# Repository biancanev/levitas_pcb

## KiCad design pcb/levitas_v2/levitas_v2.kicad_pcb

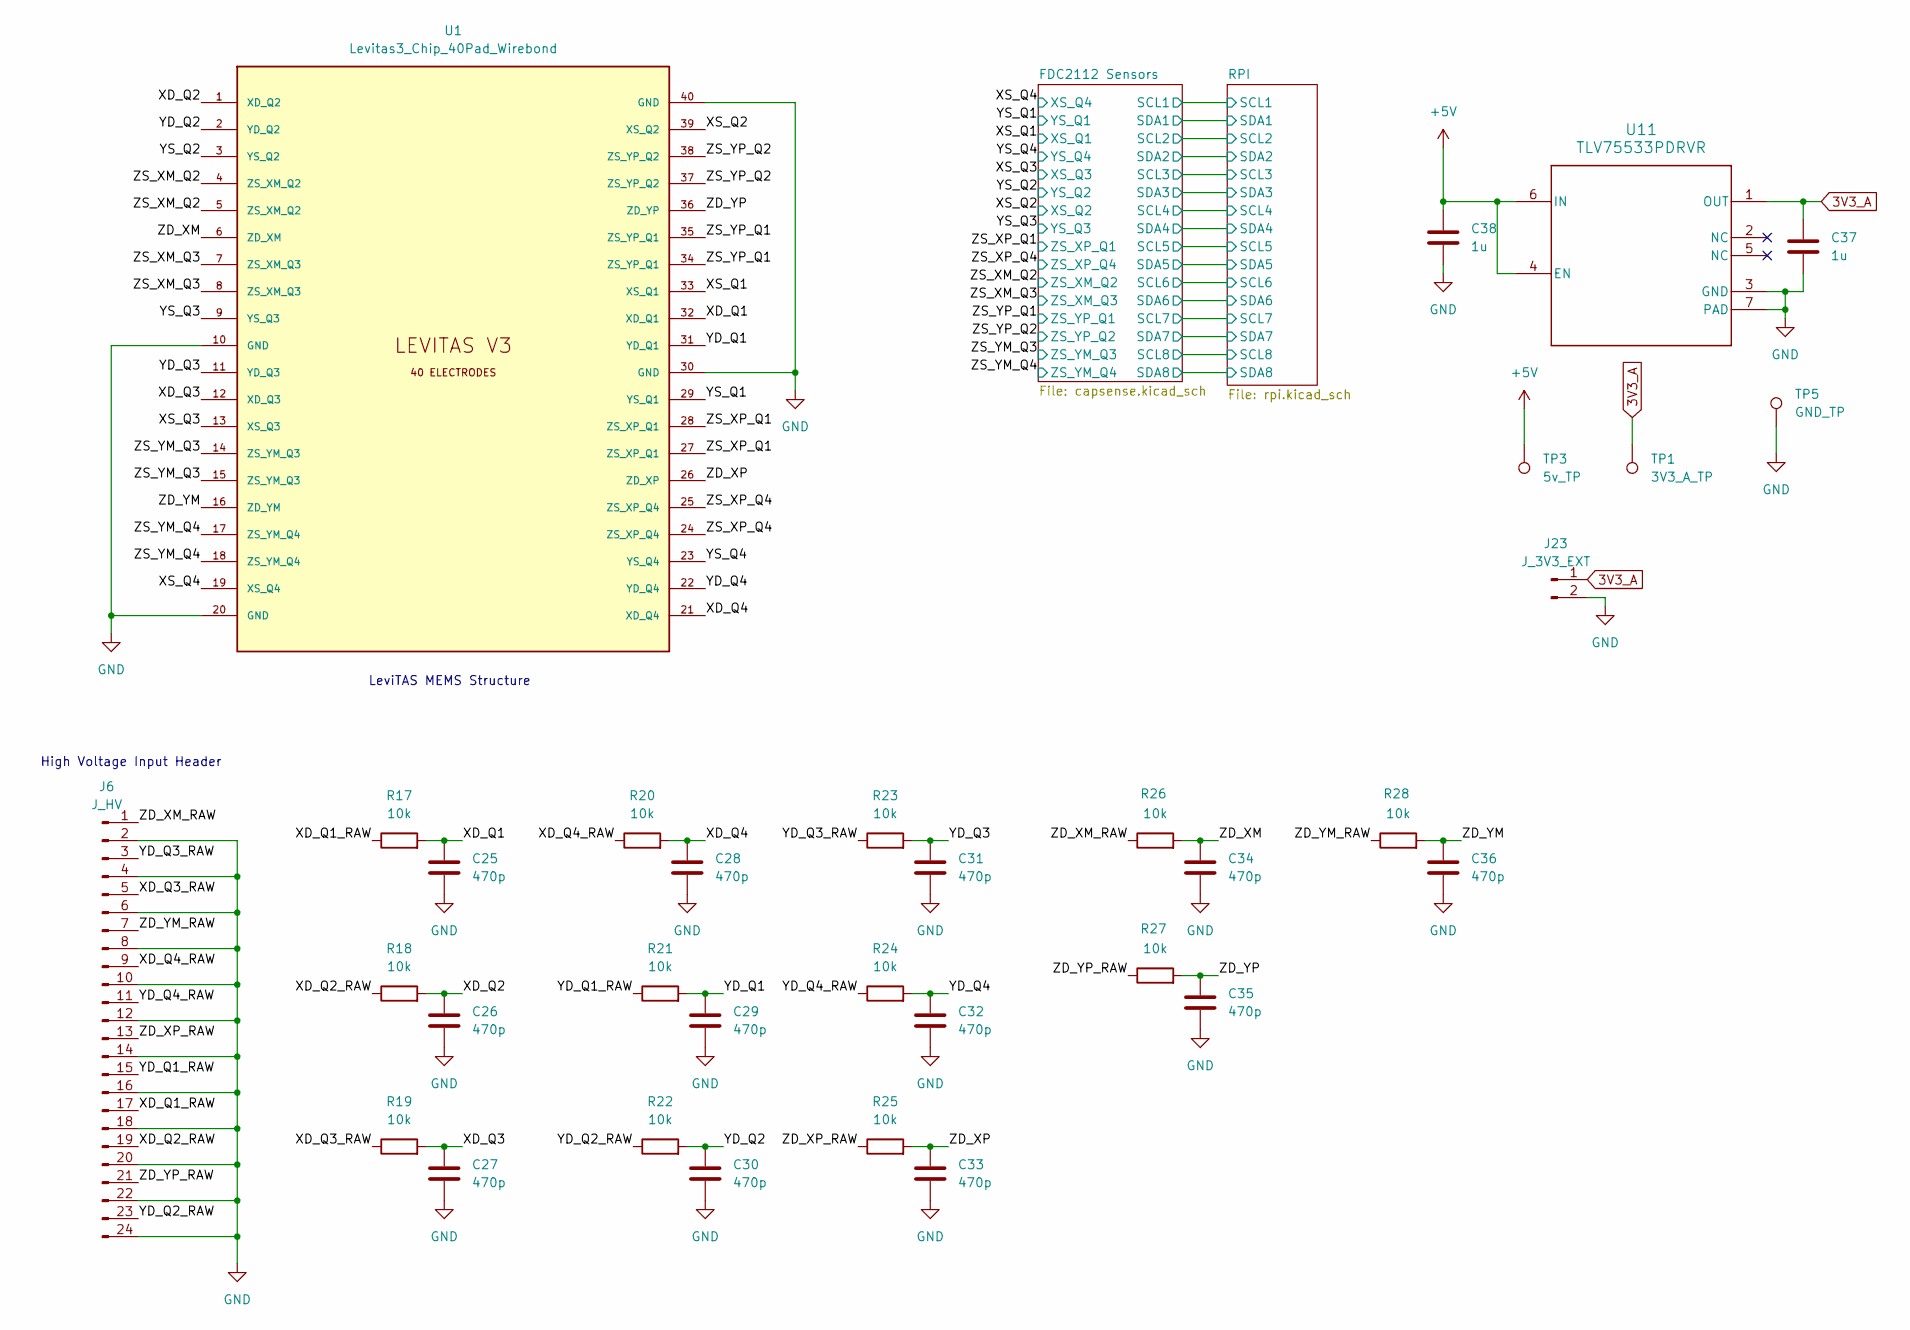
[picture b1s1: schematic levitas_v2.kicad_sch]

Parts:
C25, C26, C27, C28, C29, C30, C31, C32, C33, C34, C35, C36: 470p; C_0805_2012Metric
C37, C38: 1u; C_0805_2012Metric
J6: J_HV; PinHeader_1x24_P2.54mm_Vertical
J23: J_3V3_EXT; PinHeader_1x02_P2.54mm_Vertical
R17, R18, R19, R20, R21, R22, R23, R24, R25, R26, R27, R28: 10k; R_1206_3216Metric
TP1: 3V3_A_TP; TestPoint_Pad_D1.0mm
TP3: 5v_TP; TestPoint_Pad_D1.0mm
TP5: GND_TP; TestPoint_Pad_D1.0mm
U1: Levitas3_Chip_40Pad_Wirebond
U11: TLV75533PDRVR; DRV0006A

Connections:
/XD_Q1: C25.1, R17.2, U1.32 (XD_Q1)
/XD_Q1_RAW: J6.17, R17.1
/XD_Q2: C26.1, R18.2, U1.1 (XD_Q2)
/XD_Q2_RAW: J6.19, R18.1
/XD_Q3: C27.1, R19.2, U1.12 (XD_Q3)
/XD_Q3_RAW: J6.5, R19.1
/XD_Q4: C28.1, R20.2, U1.21 (XD_Q4)
/XD_Q4_RAW: J6.9, R20.1
/XS_Q1: U1.33 (XS_Q1); also elsewhere on the board
/XS_Q2: U1.39 (XS_Q2); also elsewhere on the board
/XS_Q3: U1.13 (XS_Q3); also elsewhere on the board
/XS_Q4: U1.19 (XS_Q4); also elsewhere on the board
/YD_Q1: C29.1, R21.2, U1.31 (YD_Q1)
/YD_Q1_RAW: J6.15, R21.1
/YD_Q2: C30.1, R22.2, U1.2 (YD_Q2)
/YD_Q2_RAW: J6.23, R22.1
/YD_Q3: C31.1, R23.2, U1.11 (YD_Q3)
/YD_Q3_RAW: J6.3, R23.1
/YD_Q4: C32.1, R24.2, U1.22 (YD_Q4)
/YD_Q4_RAW: J6.11, R24.1
/YS_Q1: U1.29 (YS_Q1); also elsewhere on the board
/YS_Q2: U1.3 (YS_Q2); also elsewhere on the board
/YS_Q3: U1.9 (YS_Q3); also elsewhere on the board
/YS_Q4: U1.23 (YS_Q4); also elsewhere on the board
/ZD_XM: C34.1, R26.2, U1.6 (ZD_XM)
/ZD_XM_RAW: J6.1, R26.1
/ZD_XP: C33.1, R25.2, U1.26 (ZD_XP)
/ZD_XP_RAW: J6.13, R25.1
/ZD_YM: C36.1, R28.2, U1.16 (ZD_YM)
/ZD_YM_RAW: J6.7, R28.1
/ZD_YP: C35.1, R27.2, U1.36 (ZD_YP)
/ZD_YP_RAW: J6.21, R27.1
/ZS_XM_Q2: U1.4 (ZS_XM_Q2), U1.5 (ZS_XM_Q2); also elsewhere on the board
/ZS_XM_Q3: U1.7 (ZS_XM_Q3), U1.8 (ZS_XM_Q3); also elsewhere on the board
/ZS_XP_Q1: U1.27 (ZS_XP_Q1), U1.28 (ZS_XP_Q1); also elsewhere on the board
/ZS_XP_Q4: U1.24 (ZS_XP_Q4), U1.25 (ZS_XP_Q4); also elsewhere on the board
/ZS_YM_Q3: U1.14 (ZS_YM_Q3), U1.15 (ZS_YM_Q3); also elsewhere on the board
/ZS_YM_Q4: U1.17 (ZS_YM_Q4), U1.18 (ZS_YM_Q4); also elsewhere on the board
/ZS_YP_Q1: U1.34 (ZS_YP_Q1), U1.35 (ZS_YP_Q1); also elsewhere on the board
/ZS_YP_Q2: U1.37 (ZS_YP_Q2), U1.38 (ZS_YP_Q2); also elsewhere on the board
GND: C25.2, C26.2, C27.2, C28.2, C29.2, C30.2, C31.2, C32.2, C33.2, C34.2, C35.2, C36.2, C37.2, C38.2, J6.2, J6.4, J6.6, J6.8, J6.10, J6.12, J6.14, J6.16, J6.18, J6.20, J6.22, J6.24, J23.2, TP5.1 (1_1), U1.10 (GND), U1.20 (GND), U1.30 (GND), U1.40 (GND), U11.3 (GND), U11.7 (PAD); also elsewhere on the board

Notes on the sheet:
High Voltage Input Header
LeviTAS MEMS Structure

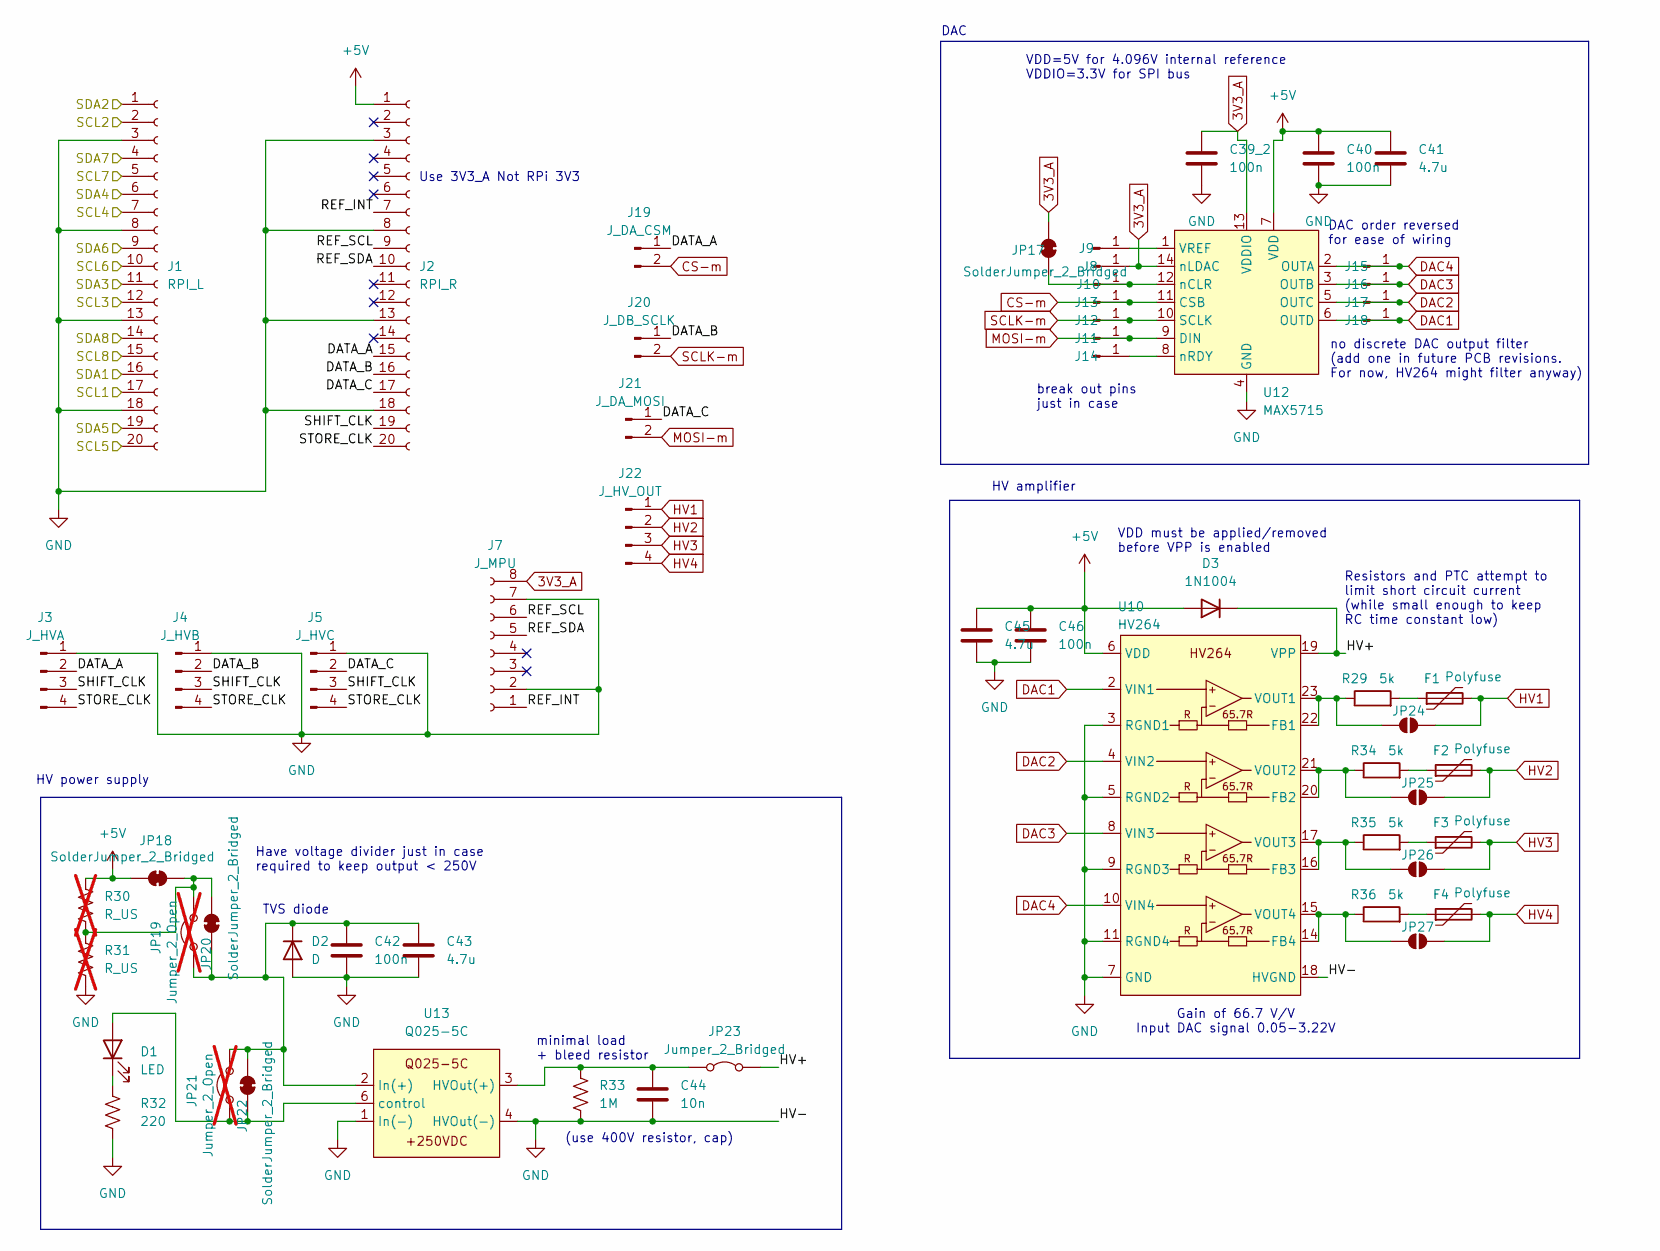
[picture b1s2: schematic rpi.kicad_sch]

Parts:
C39_2, C40, C42, C46: 100n; C_0603_1608Metric
C41, C43, C45: 4.7u; C_0805_2012Metric
C44: 10n; C_Disc_D7.5mm_W2.5mm_P5.00mm
D1: LED; LED_D5.0mm
D2: D; D_DO-41_SOD81_P10.16mm_Horizontal
D3: 1N1004; D_DO-41_SOD81_P10.16mm_Horizontal
F1, F2, F3, F4: Polyfuse; R_Axial_DIN0207_L6.3mm_D2.5mm_P7.62mm_Horizontal
J1: RPI_L; PinSocket_1x20_P2.54mm_Vertical
J2: RPI_R; PinSocket_1x20_P2.54mm_Vertical
J3: J_HVA; PinHeader_1x04_P2.54mm_Vertical
J4: J_HVB; PinHeader_1x04_P2.54mm_Vertical
J5: J_HVC; PinHeader_1x04_P2.54mm_Vertical
J7: J_MPU; PinSocket_1x08_P2.54mm_Vertical
J8, J9, J10, J11, J12, J13, J14, J15, J16, J17, J18: Conn_01x01_Pin; TestPoint_Pad_D2.0mm
J19: J_DA_CSM; PinHeader_1x02_P2.54mm_Vertical
J20: J_DB_SCLK; PinHeader_1x02_P2.54mm_Vertical
J21: J_DA_MOSI; PinHeader_1x02_P2.54mm_Vertical
J22: J_HV_OUT; PinHeader_1x04_P2.54mm_Vertical
JP17, JP18, JP20, JP22: SolderJumper_2_Bridged; SolderJumper-2_P1.3mm_Bridged_RoundedPad1.0x1.5mm
JP19, JP21: Jumper_2_Open; PinHeader_1x02_P2.54mm_Vertical; not fitted
JP23: Jumper_2_Bridged; PinHeader_1x02_P2.54mm_Vertical
JP24, JP25, JP26, JP27: SolderJumper_2_Open; SolderJumper-2_P1.3mm_Open_RoundedPad1.0x1.5mm
R29, R34, R35, R36: 5k; R_Axial_DIN0207_L6.3mm_D2.5mm_P7.62mm_Horizontal
R30, R31: R_US; R_Axial_DIN0207_L6.3mm_D2.5mm_P7.62mm_Horizontal; not fitted
R32: 220; R_Axial_DIN0207_L6.3mm_D2.5mm_P7.62mm_Horizontal
R33: 1M; R_Axial_DIN0207_L6.3mm_D2.5mm_P7.62mm_Horizontal
U10: HV264; TSSOP-24_4.4x7.8mm_P0.65mm
U12: MAX5715; TSSOP-14_4.4x5mm_P0.65mm
U13: Q025-5C

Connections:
/FDC2112 Sensors/SCL1: J1.17; also elsewhere on the board
/FDC2112 Sensors/SCL2: J1.2; also elsewhere on the board
/FDC2112 Sensors/SCL3: J1.12; also elsewhere on the board
/FDC2112 Sensors/SCL4: J1.7; also elsewhere on the board
/FDC2112 Sensors/SCL5: J1.20; also elsewhere on the board
/FDC2112 Sensors/SCL6: J1.10; also elsewhere on the board
/FDC2112 Sensors/SCL7: J1.5; also elsewhere on the board
/FDC2112 Sensors/SCL8: J1.15; also elsewhere on the board
/FDC2112 Sensors/SDA1: J1.16; also elsewhere on the board
/FDC2112 Sensors/SDA2: J1.1; also elsewhere on the board
/FDC2112 Sensors/SDA3: J1.11; also elsewhere on the board
/FDC2112 Sensors/SDA4: J1.6; also elsewhere on the board
/FDC2112 Sensors/SDA5: J1.19; also elsewhere on the board
/FDC2112 Sensors/SDA6: J1.9; also elsewhere on the board
/FDC2112 Sensors/SDA7: J1.4; also elsewhere on the board
/FDC2112 Sensors/SDA8: J1.14; also elsewhere on the board
/RPI/DATA_A: J2.15, J3.2, J19.1
/RPI/DATA_B: J2.16, J4.2, J20.1
/RPI/DATA_C: J2.17, J5.2, J21.1
/RPI/HV+: D3.1 (K), JP23.2 (B), U10.19 (VPP)
/RPI/REF_INT: J2.7, J7.1
/RPI/REF_SCL: J2.9, J7.6
/RPI/REF_SDA: J2.10, J7.5
/RPI/SHIFT_CLK: J2.19, J3.3, J4.3, J5.3
/RPI/STORE_CLK: J2.20, J3.4, J4.4, J5.4
CS-m: J13.1, J19.2, U12.11 (CSB)
DAC1: J18.1, U10.2 (VIN1), U12.6 (OUTD)
DAC2: J17.1, U10.4 (VIN2), U12.5 (OUTC)
DAC3: J16.1, U10.8 (VIN3), U12.3 (OUTB)
DAC4: J15.1, U10.10 (VIN4), U12.2 (OUTA)
GND: C39_2.2, C40.2, C41.2, C42.2, C43.2, C44.2, C45.2, C46.2, D2.2 (A), J1.3, J1.8, J1.13, J1.18, J2.3, J2.8, J2.13, J2.18, J3.1, J4.1, J5.1, J7.2, J7.7, R31.2, R32.2, R33.2, U10.3 (RGND1), U10.5 (RGND2), U10.7 (GND), U10.9 (RGND3), U10.11 (RGND4), U10.18 (HVGND), U12.4 (GND), U13.1 (In(-)), U13.4 (HVOut(-)); also elsewhere on the board
HV1: F1.2, J22.1, JP24.2 (B)
HV2: F2.2, J22.2, JP25.2 (B)
HV3: F3.2, J22.3, JP26.2 (B)
HV4: F4.2, J22.4, JP27.2 (B)
MOSI-m: J11.1, J21.2, U12.9 (DIN)
unnamed: D1.2 (A), JP21.1 (A), JP22.1 (A), U13.6 (control)
unnamed: D1.1 (K), R32.1
unnamed: C42.1, C43.1, D2.1 (K), JP19.1 (A), JP20.1 (A), JP21.2 (B), JP22.2 (B), U13.2 (In(+))
unnamed: F1.1, R29.2
unnamed: F2.1, R34.2
unnamed: F3.1, R35.2
unnamed: F4.1, R36.2
unnamed: J9.1, U12.1 (VREF)
unnamed: J10.1, JP17.2 (B), U12.12 (nCLR)
unnamed: J14.1, U12.8 (nRDY)
unnamed: JP18.1 (A), JP19.2 (B), JP20.2 (B), R30.2, R31.1
unnamed: C44.1, JP23.1 (A), R33.1, U13.3 (HVOut(+))
unnamed: JP24.1 (A), R29.1, U10.22 (FB1), U10.23 (VOUT1)
unnamed: JP25.1 (A), R34.1, U10.20 (FB2), U10.21 (VOUT2)
unnamed: JP26.1 (A), R35.1, U10.16 (FB3), U10.17 (VOUT3)
unnamed: JP27.1 (A), R36.1, U10.14 (FB4), U10.15 (VOUT4)
SCLK-m: J12.1, J20.2, U12.10 (SCLK)

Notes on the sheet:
VDD=5V for 4.096V internal reference VDDIO=3.3V for SPI bus
DAC
VDD must be applied/removed before VPP is enabled
Resistors and PTC attempt to limit short circuit current (while small enough to keep RC time constant low)
TVS diode
DAC order reversed for ease of wiring
minimal load + bleed resistor
Have voltage divider just in case required to keep output < 250V
HV power supply
(use 400V resistor, cap)
break out pins just in case
Use 3V3_A Not RPi 3V3
no discrete DAC output filter (add one in future PCB revisions. For now, HV264 might filter anyway)
Gain of 66.7 V/V Input DAC signal 0.05-3.22V
HV amplifier

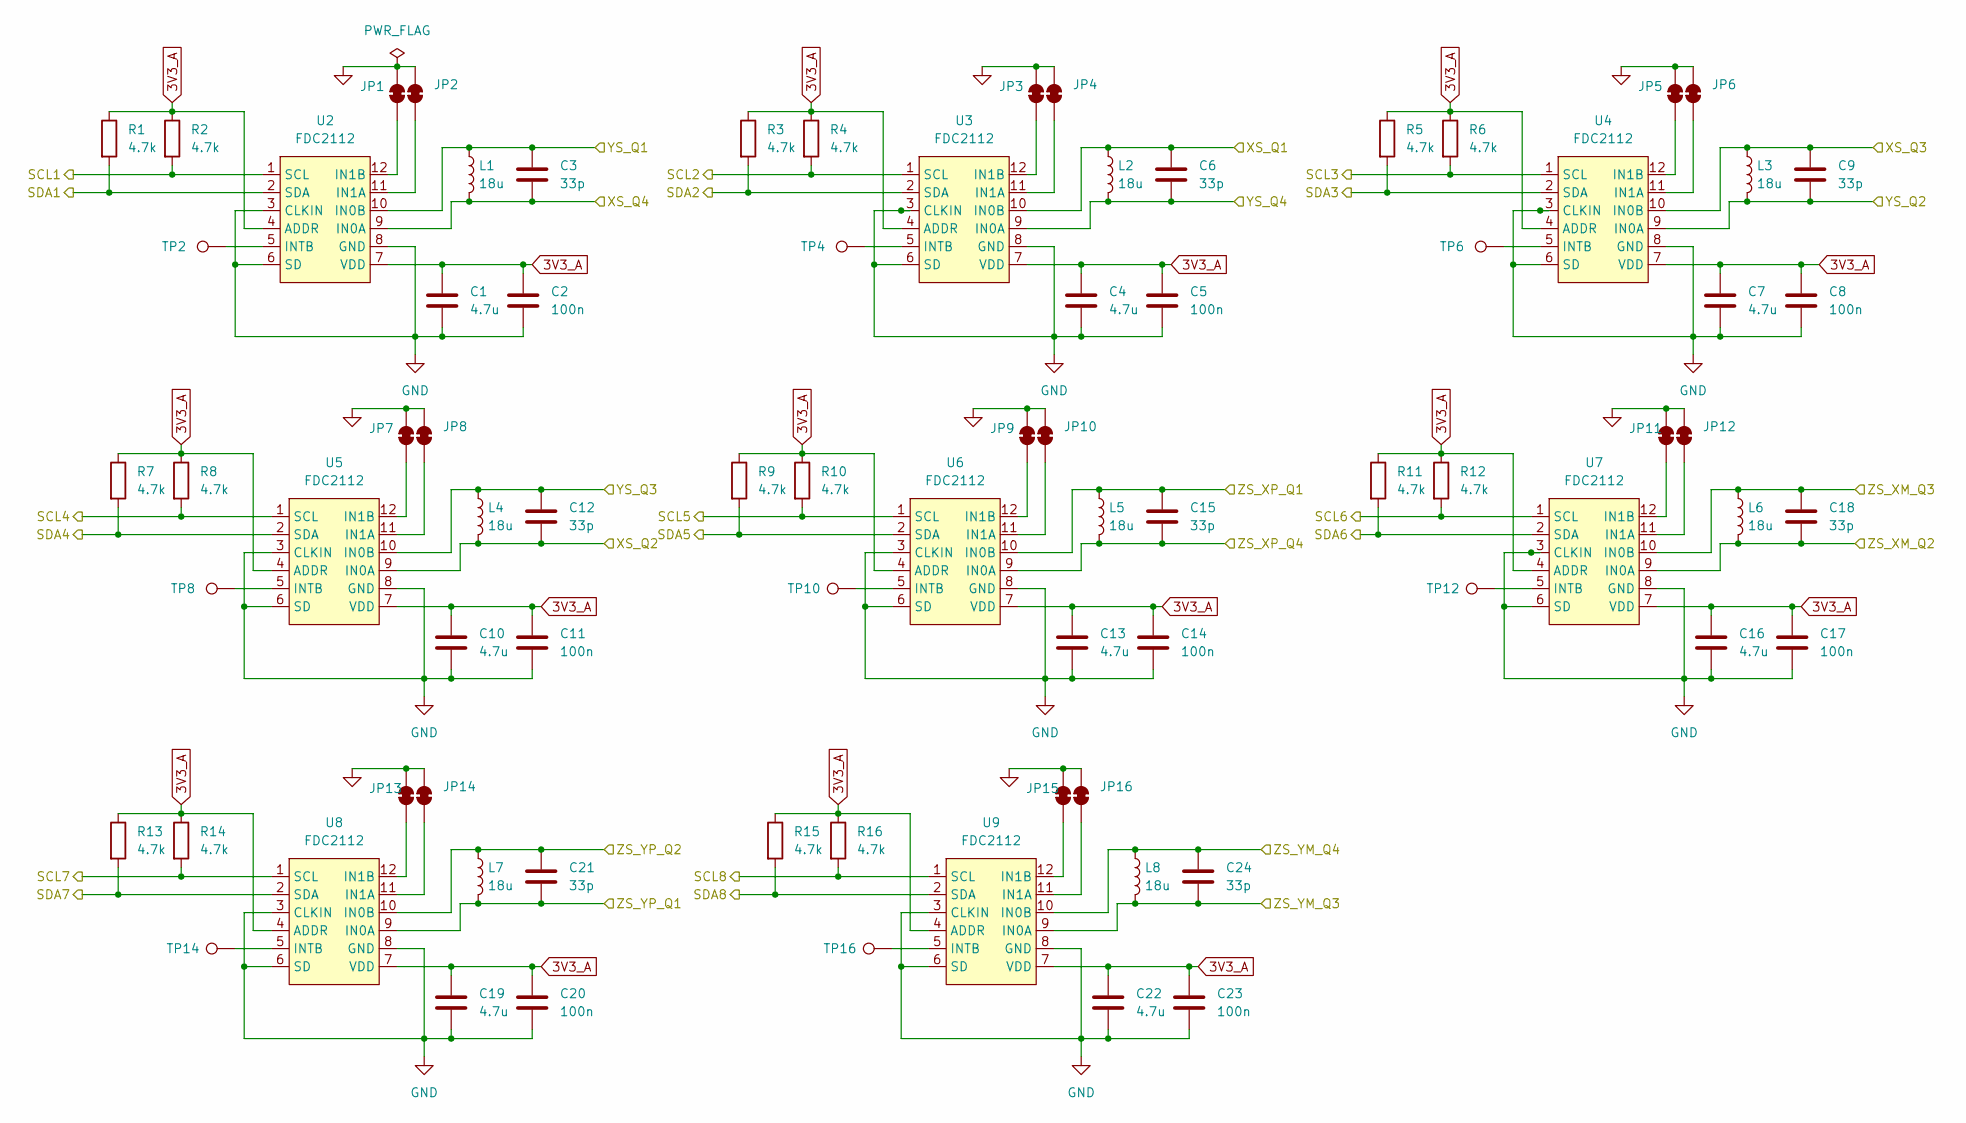
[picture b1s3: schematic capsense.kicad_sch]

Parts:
C1, C4, C7, C10, C13, C16, C19, C22: 4.7u; C_0805_2012Metric
C2, C5, C8, C11, C14, C17, C20, C23: 100n; C_0603_1608Metric
C3, C6, C9, C12, C15, C18, C21, C24: 33p; C_0603_1608Metric
JP1, JP2, JP3, JP4, JP5, JP6, JP7, JP8, JP9, JP10, JP11, JP12, JP13, JP14, JP15, JP16: SolderJumper_2_Bridged; SolderJumper-2_P1.3mm_Bridged_RoundedPad1.0x1.5mm
L1, L2, L3, L4, L5, L6, L7, L8: 18u; L_0603_1608Metric
R1, R2, R3, R4, R5, R6, R7, R8, R9, R10, R11, R12, R13, R14, R15, R16: 4.7k; R_0603_1608Metric
TP2, TP4, TP6, TP8, TP10, TP12, TP14, TP16: TestPoint; TestPoint_Pad_D1.0mm
U2, U3, U4, U5, U6, U7, U8, U9: FDC2112; WSON-12-1EP_4x4mm_P0.5mm_EP2.6x3mm

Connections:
/FDC2112 Sensors/SCL1: R2.2, U2.1 (SCL); also elsewhere on the board
/FDC2112 Sensors/SCL2: R4.2, U3.1 (SCL); also elsewhere on the board
/FDC2112 Sensors/SCL3: R6.2, U4.1 (SCL); also elsewhere on the board
/FDC2112 Sensors/SCL4: R8.2, U5.1 (SCL); also elsewhere on the board
/FDC2112 Sensors/SCL5: R10.2, U6.1 (SCL); also elsewhere on the board
/FDC2112 Sensors/SCL6: R12.2, U7.1 (SCL); also elsewhere on the board
/FDC2112 Sensors/SCL7: R14.2, U8.1 (SCL); also elsewhere on the board
/FDC2112 Sensors/SCL8: R16.2, U9.1 (SCL); also elsewhere on the board
/FDC2112 Sensors/SDA1: R1.2, U2.2 (SDA); also elsewhere on the board
/FDC2112 Sensors/SDA2: R3.2, U3.2 (SDA); also elsewhere on the board
/FDC2112 Sensors/SDA3: R5.2, U4.2 (SDA); also elsewhere on the board
/FDC2112 Sensors/SDA4: R7.2, U5.2 (SDA); also elsewhere on the board
/FDC2112 Sensors/SDA5: R9.2, U6.2 (SDA); also elsewhere on the board
/FDC2112 Sensors/SDA6: R11.2, U7.2 (SDA); also elsewhere on the board
/FDC2112 Sensors/SDA7: R13.2, U8.2 (SDA); also elsewhere on the board
/FDC2112 Sensors/SDA8: R15.2, U9.2 (SDA); also elsewhere on the board
/XS_Q1: C6.1, L2.1, U3.10 (IN0B); also elsewhere on the board
/XS_Q2: C12.2, L4.2, U5.9 (IN0A); also elsewhere on the board
/XS_Q3: C9.1, L3.1, U4.10 (IN0B); also elsewhere on the board
/XS_Q4: C3.2, L1.2, U2.9 (IN0A); also elsewhere on the board
/YS_Q1: C3.1, L1.1, U2.10 (IN0B); also elsewhere on the board
/YS_Q2: C9.2, L3.2, U4.9 (IN0A); also elsewhere on the board
/YS_Q3: C12.1, L4.1, U5.10 (IN0B); also elsewhere on the board
/YS_Q4: C6.2, L2.2, U3.9 (IN0A); also elsewhere on the board
/ZS_XM_Q2: C18.2, L6.2, U7.9 (IN0A); also elsewhere on the board
/ZS_XM_Q3: C18.1, L6.1, U7.10 (IN0B); also elsewhere on the board
/ZS_XP_Q1: C15.1, L5.1, U6.10 (IN0B); also elsewhere on the board
/ZS_XP_Q4: C15.2, L5.2, U6.9 (IN0A); also elsewhere on the board
/ZS_YM_Q3: C24.2, L8.2, U9.9 (IN0A); also elsewhere on the board
/ZS_YM_Q4: C24.1, L8.1, U9.10 (IN0B); also elsewhere on the board
/ZS_YP_Q1: C21.2, L7.2, U8.9 (IN0A); also elsewhere on the board
/ZS_YP_Q2: C21.1, L7.1, U8.10 (IN0B); also elsewhere on the board
GND: C1.2, C2.2, C4.2, C5.2, C7.2, C8.2, C10.2, C11.2, C13.2, C14.2, C16.2, C17.2, C19.2, C20.2, C22.2, C23.2, JP1.2 (B), JP2.2 (B), JP3.2 (B), JP4.2 (B), JP5.2 (B), JP6.2 (B), JP7.2 (B), JP8.2 (B), JP9.2 (B), JP10.2 (B), JP11.2 (B), JP12.2 (B), JP13.2 (B), JP14.2 (B), JP15.2 (B), JP16.2 (B), U2.3 (CLKIN), U2.6 (SD), U2.8 (GND), U3.3 (CLKIN), U3.6 (SD), U3.8 (GND), U4.3 (CLKIN), U4.6 (SD), U4.8 (GND), U5.3 (CLKIN), U5.6 (SD), U5.8 (GND), U6.3 (CLKIN), U6.6 (SD), U6.8 (GND), U7.3 (CLKIN), U7.6 (SD), U7.8 (GND), U8.3 (CLKIN), U8.6 (SD), U8.8 (GND), U9.3 (CLKIN), U9.6 (SD), U9.8 (GND); also elsewhere on the board
unnamed: JP1.1 (A), U2.12 (IN1B)
unnamed: JP2.1 (A), U2.11 (IN1A)
unnamed: JP3.1 (A), U3.12 (IN1B)
unnamed: JP4.1 (A), U3.11 (IN1A)
unnamed: JP5.1 (A), U4.12 (IN1B)
unnamed: JP6.1 (A), U4.11 (IN1A)
unnamed: JP7.1 (A), U5.12 (IN1B)
unnamed: JP8.1 (A), U5.11 (IN1A)
unnamed: JP9.1 (A), U6.12 (IN1B)
unnamed: JP10.1 (A), U6.11 (IN1A)
unnamed: JP11.1 (A), U7.12 (IN1B)
unnamed: JP12.1 (A), U7.11 (IN1A)
unnamed: JP13.1 (A), U8.12 (IN1B)
unnamed: JP14.1 (A), U8.11 (IN1A)
unnamed: JP15.1 (A), U9.12 (IN1B)
unnamed: JP16.1 (A), U9.11 (IN1A)
unnamed: TP2.1 (1_1), U2.5 (INTB)
unnamed: TP4.1 (1_1), U3.5 (INTB)
unnamed: TP6.1 (1_1), U4.5 (INTB)
unnamed: TP8.1 (1_1), U5.5 (INTB)
unnamed: TP10.1 (1_1), U6.5 (INTB)
unnamed: TP12.1 (1_1), U7.5 (INTB)
unnamed: TP14.1 (1_1), U8.5 (INTB)
unnamed: TP16.1 (1_1), U9.5 (INTB)

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
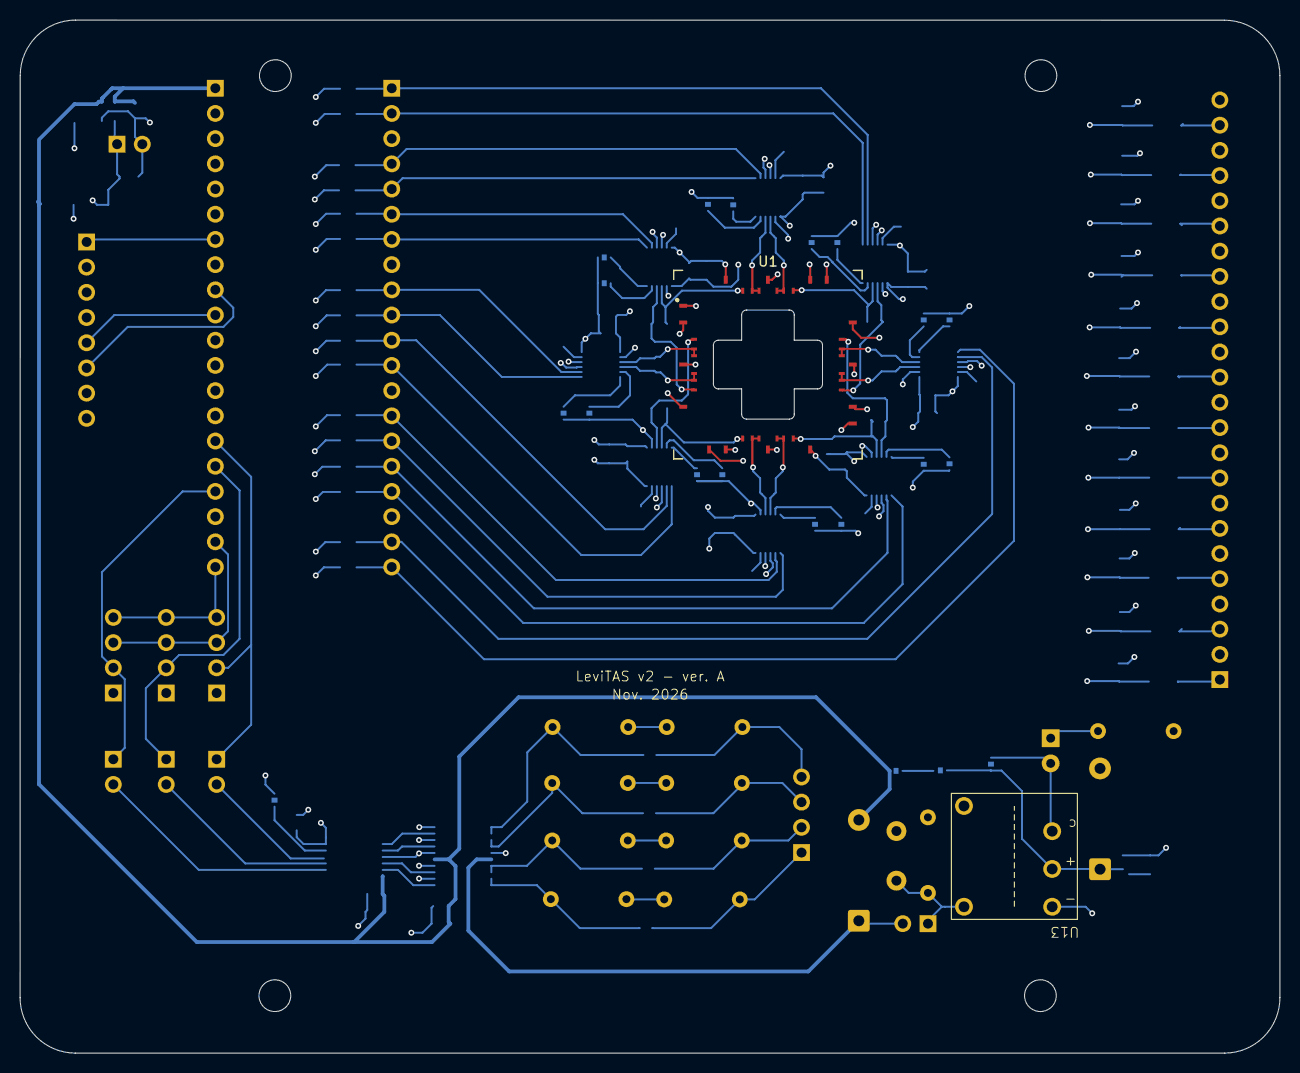
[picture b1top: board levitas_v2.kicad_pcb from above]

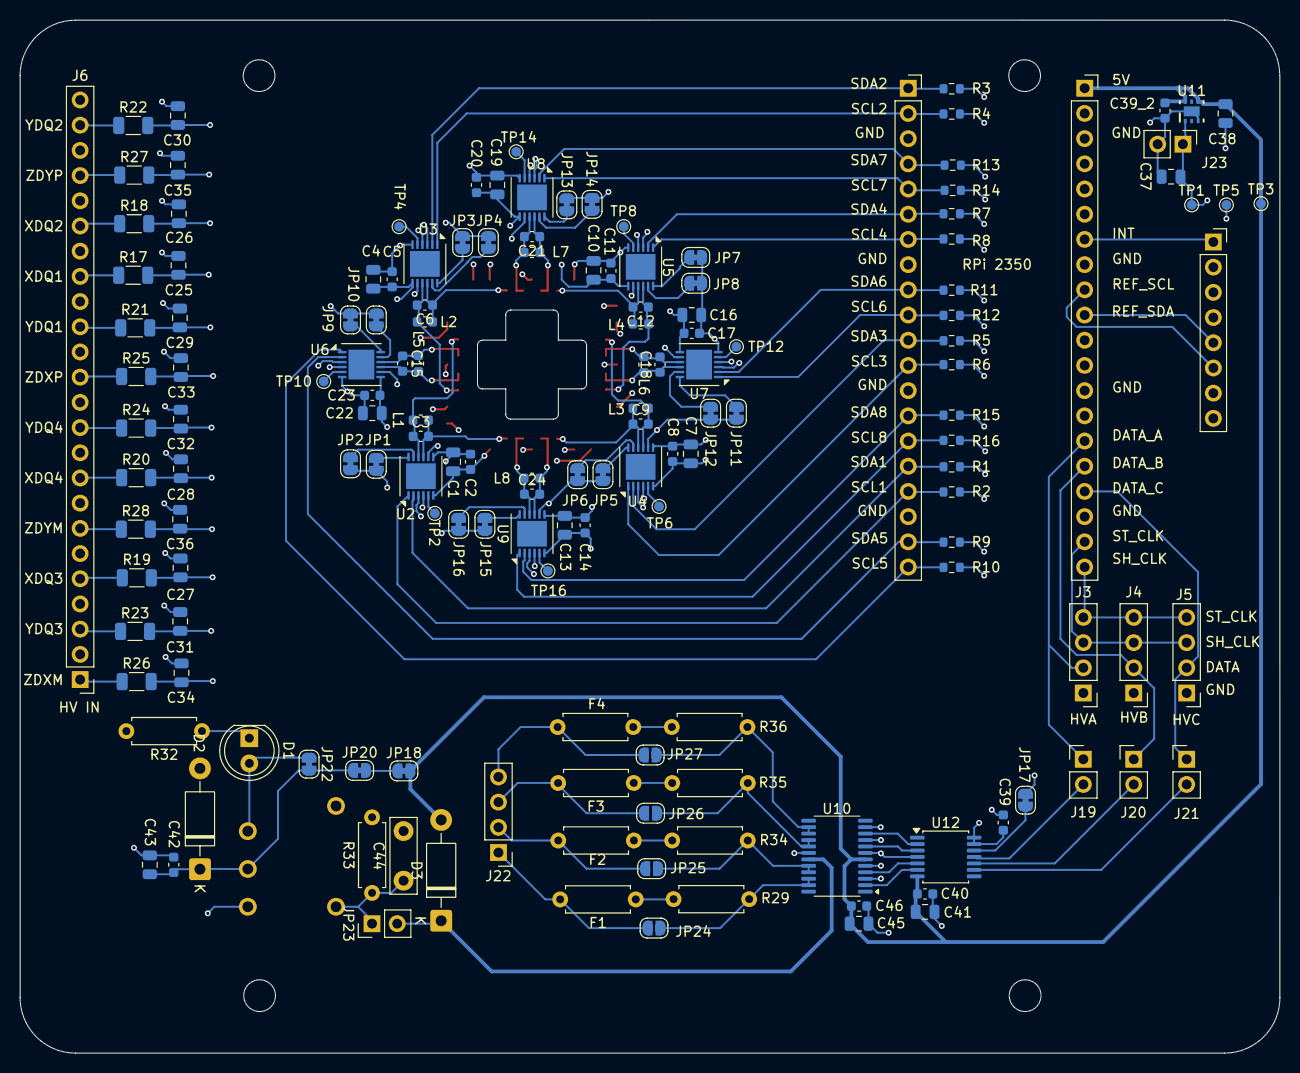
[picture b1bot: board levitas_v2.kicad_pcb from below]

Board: 4 copper layers, 127.0 x 104.1 mm, 161 parts (155 on the bottom side), 117 nets.

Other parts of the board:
C39: 100n; C_0603_1608Metric
M3_H1, M3_H2, M3_H3, M3_H4: MountingHole_3.2mm_M3

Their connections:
GND: C39.2; also elsewhere on the board

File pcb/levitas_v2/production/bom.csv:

Designator,Footprint,Quantity,Value,LCSC Part #
"C1, C10, C13, C16, C19, C22, C4, C41, C43, C45, C7",0805,11,4.7u,
"C11, C14, C17, C2, C20, C23, C39, C40, C42, C46, C5, C8",0603,12,100n,
"C12, C15, C18, C21, C24, C3, C6, C9",0603,8,33p,
"C25, C26, C27, C28, C29, C30, C31, C32, C33, C34, C35, C36",0805,12,470p,
"C37, C38",0805,2,1u,
C39_2,0603,1,0.1u,
C44,C_Disc_D7.5mm_W2.5mm_P5.00mm,1,10n,
D1,LED_D5.0mm,1,LED,
D2,D_DO-41_SOD81_P10.16mm_Horizontal,1,D,
D3,D_DO-41_SOD81_P10.16mm_Horizontal,1,1N1004,
"F1, F2, F3, F4",R_Axial_DIN0207_L6.3mm_D2.5mm_P7.62mm_Horizontal,4,Polyfuse,
J1,PinSocket_1x20_P2.54mm_Vertical,1,RPI_L,
J19,PinHeader_1x02_P2.54mm_Vertical,1,J_DA_CSM,
J2,PinSocket_1x20_P2.54mm_Vertical,1,RPI_R,
J20,PinHeader_1x02_P2.54mm_Vertical,1,J_DB_SCLK,
J21,PinHeader_1x02_P2.54mm_Vertical,1,J_DA_MOSI,
J22,PinHeader_1x04_P2.54mm_Vertical,1,J_HV_OUT,
J23,PinHeader_1x02_P2.54mm_Vertical,1,J_3V3_EXT,
J3,PinHeader_1x04_P2.54mm_Vertical,1,J_HVA,
J4,PinHeader_1x04_P2.54mm_Vertical,1,J_HVB,
J5,PinHeader_1x04_P2.54mm_Vertical,1,J_HVC,
J6,PinHeader_1x24_P2.54mm_Vertical,1,J_HV,
J7,PinSocket_1x08_P2.54mm_Vertical,1,J_MPU,
JP23,PinHeader_1x02_P2.54mm_Vertical,1,Jumper_2_Bridged,
"L1, L2, L3, L4, L5, L6, L7, L8",0603,8,18u,
"R1, R10, R11, R12, R13, R14, R15, R16, R2, R3, R4, R5, R6, R7, R8, R9",0603,16,4.7k,
"R17, R18, R19, R20, R21, R22, R23, R24, R25, R26, R27, R28",1206,12,10k,
"R29, R34, R35, R36",R_Axial_DIN0207_L6.3mm_D2.5mm_P7.62mm_Horizontal,4,5k,
R32,R_Axial_DIN0207_L6.3mm_D2.5mm_P7.62mm_Horizontal,1,220,
R33,R_Axial_DIN0207_L6.3mm_D2.5mm_P7.62mm_Horizontal,1,1M,
TP1,TestPoint_Pad_D1.0mm,1,3V3_A_TP,
"TP10, TP12, TP14, TP16, TP2, TP4, TP6, TP8",TestPoint_Pad_D1.0mm,8,TestPoint,
TP3,TestPoint_Pad_D1.0mm,1,5v_TP,
TP5,TestPoint_Pad_D1.0mm,1,GND_TP,
U1,Levitas3_Chip_40Pad_Wirebond,1,Levitas3_Chip_40Pad_Wirebond,
U10,TSSOP-24_4.4x7.8mm_P0.65mm,1,HV264,
U11,DRV0006A,1,TLV75533PDRVR,
U12,TSSOP-14_4.4x5mm_P0.65mm,1,MAX5715,
U13,Q025-5C,1,Q025-5C,
"U2, U3, U4, U5, U6, U7, U8, U9",WSON-12-1EP_4x4mm_P0.5mm_EP2.6x3mm,8,FDC2112,
